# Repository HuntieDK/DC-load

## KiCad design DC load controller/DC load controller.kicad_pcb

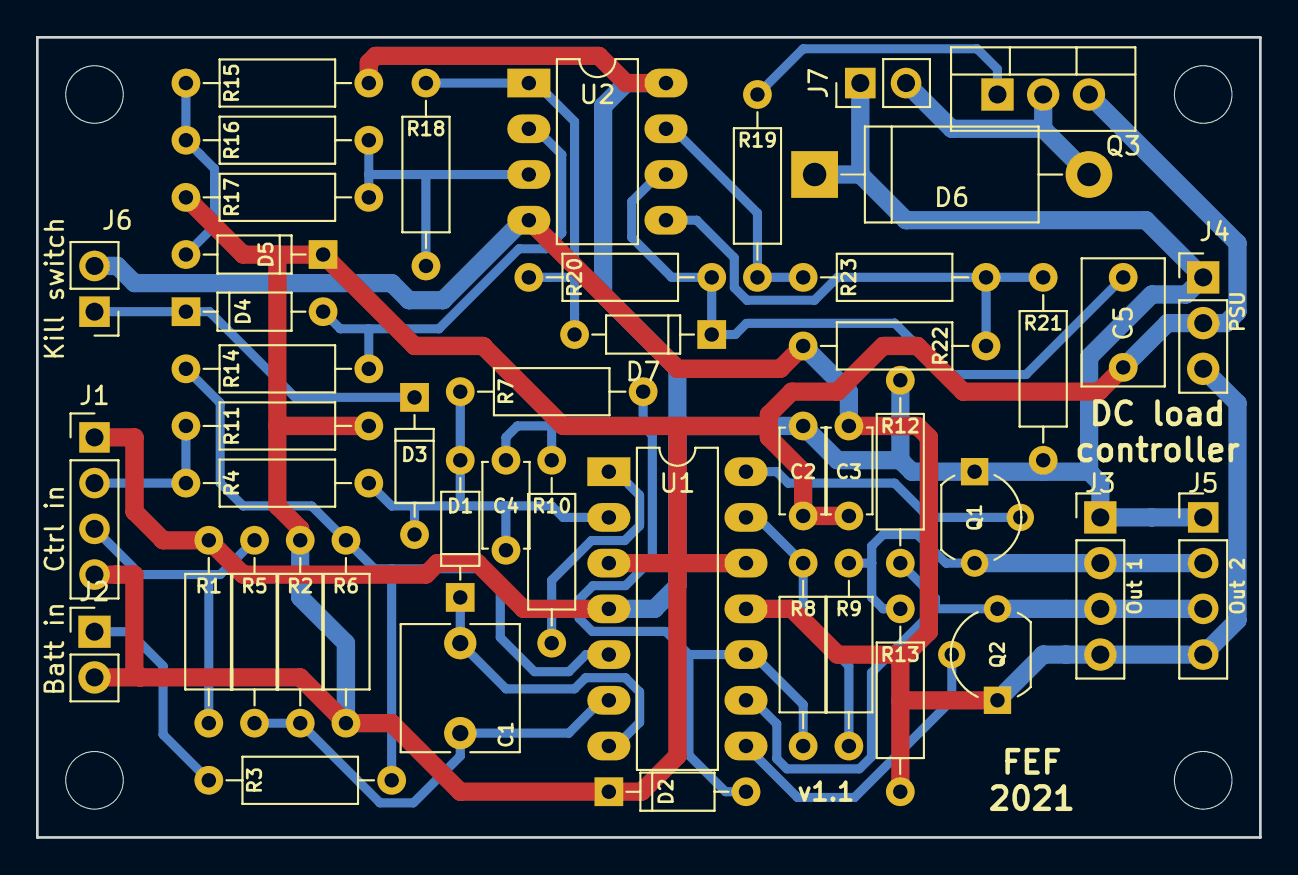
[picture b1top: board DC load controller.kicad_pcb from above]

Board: 2 copper layers, 67.9 x 44.5 mm, 51 parts (0 on the bottom side), 27 nets.

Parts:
C1: 2u2; C_Rect_L7.0mm_W6.5mm_P5.00mm
C2, C3: 100n; C_Disc_D4.7mm_W2.5mm_P5.00mm
C4: 10n; C_Disc_D4.7mm_W2.5mm_P5.00mm
C5: 220n; C_Rect_L7.0mm_W4.5mm_P5.00mm
D1, D3, D4, D5, D7: 1n4148; D_DO-35_SOD27_P7.62mm_Horizontal
D2: 5v6; D_DO-35_SOD27_P7.62mm_Horizontal
D6: 1n5403; D_DO-201_P15.24mm_Horizontal
J1: Ctrl In; PinHeader_1x04_P2.54mm_Vertical
J2: Batt in; Pin_Header_Straight_1x02_Pitch2.54mm
J3: Ctrl Out 1; Pin_Header_Straight_1x04_Pitch2.54mm
J4: Pwr in; Pin_Header_Straight_1x03_Pitch2.54mm
J5: Ctrl Out 2; Pin_Header_Straight_1x04_Pitch2.54mm
J6: Killswitch; Pin_Header_Straight_1x02_Pitch2.54mm
J7: Relay out; Pin_Header_Straight_1x02_Pitch2.54mm
M1, M2, M3, M4: 3mm; MountingHole_3.2mm_M3
Q1: BC337; TO-92_Molded_Wide
Q2: BC327; TO-92_Molded_Wide
Q3: IRF540N; TO-220-3_Vertical
R1: 66k5; R_Axial_DIN0207_L6.3mm_D2.5mm_P10.16mm_Horizontal
R2, R3, R4: 20k; R_Axial_DIN0207_L6.3mm_D2.5mm_P10.16mm_Horizontal
R5, R6: 2k; R_Axial_DIN0207_L6.3mm_D2.5mm_P10.16mm_Horizontal
R7, R8, R9, R15: 10k; R_Axial_DIN0207_L6.3mm_D2.5mm_P10.16mm_Horizontal
R10: 953; R_Axial_DIN0207_L6.3mm_D2.5mm_P10.16mm_Horizontal
R11, R12, R13, R23: 1k; R_Axial_DIN0207_L6.3mm_D2.5mm_P10.16mm_Horizontal
R14, R21, R22: 100k; R_Axial_DIN0207_L6.3mm_D2.5mm_P10.16mm_Horizontal
R16: 6k04; R_Axial_DIN0207_L6.3mm_D2.5mm_P10.16mm_Horizontal
R17, R19: 100; R_Axial_DIN0207_L6.3mm_D2.5mm_P10.16mm_Horizontal
R18: 1M2; R_Axial_DIN0207_L6.3mm_D2.5mm_P10.16mm_Horizontal
R20: 1M; R_Axial_DIN0207_L6.3mm_D2.5mm_P10.16mm_Horizontal
U1: LM324; DIP-14_W7.62mm_LongPads
U2: LM358; DIP-8_W7.62mm_LongPads

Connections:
GND: C2.2, C3.1, C5.2, D2.1, D5.1, J1.4, J2.2, J4.2, Q3.3, R5.2, R6.2, R11.2, R17.2, U1.3, U1.12
unnamed: C1.1, D1.1, U1.7
unnamed: C1.2, R2.2, R5.1, U1.6
unnamed: C4.1, D1.2, D3.2, R4.1, R7.2, U1.2
unnamed: C4.2, D2.2, R7.1, R8.2, R10.1, U1.10
unnamed: C5.1, D7.1, R20.2, U2.6
unnamed: D3.1, D4.1, J6.1
unnamed: D4.2, R14.1, U2.2
unnamed: D5.2, R15.1, R16.1
unnamed: D6.2, J7.2, Q3.2
unnamed: D7.2, R18.1, R20.1, U2.1
unnamed: J1.2, R4.2, R11.1
unnamed: J1.3, R1.2, R2.1
unnamed: J2.1, R3.2
unnamed: J3.2, J5.2, Q1.3, R9.2, R13.1
unnamed: J3.3, J5.3, Q2.3, R12.2, U1.9
unnamed: Q1.2, U1.14
unnamed: Q2.2, U1.8
unnamed: Q3.1, R19.1
unnamed: R8.1, R9.1, U1.13
unnamed: R10.2, U1.1
unnamed: R3.1, R6.1, R14.2, U1.5
unnamed: R16.2, R17.1, R18.2, U2.3
unnamed: R19.2, R23.1, U2.7
unnamed: R21.2, R22.1, R23.2, U2.5
VDD: C2.1, D6.1, J1.1, J3.1, J4.1, J5.1, J7.1, Q1.1, R1.1, R12.1, R15.2, R21.1, U1.4, U2.8
VSS: C3.2, J3.4, J4.3, J5.4, J6.2, Q2.1, R13.2, R22.2, U1.11, U2.4

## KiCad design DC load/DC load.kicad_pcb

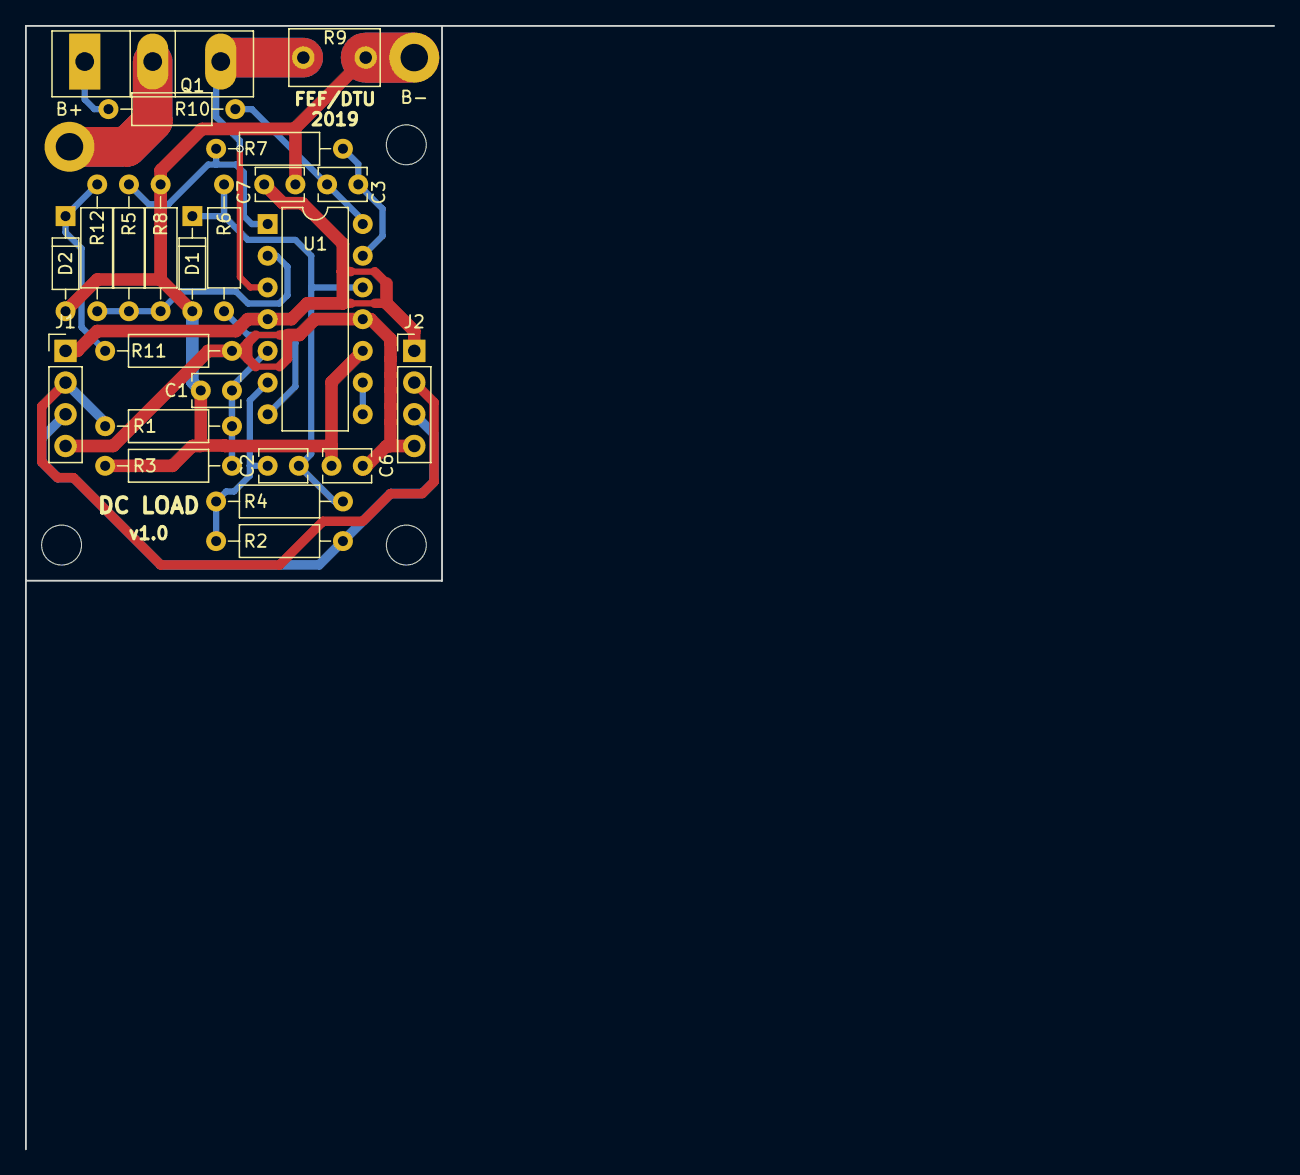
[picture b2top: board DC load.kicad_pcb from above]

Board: 2 copper layers, 100.0 x 90.0 mm, 28 parts (0 on the bottom side), 18 nets.

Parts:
C1, C2, C6, C7: 10n; C_Disc_D3.8mm_W2.6mm_P2.50mm
C3: 22n; C_Disc_D3.8mm_W2.6mm_P2.50mm
D1: 3v0/5mA; D_DO-35_SOD27_P7.62mm_Horizontal
D2: 1n4148; D_DO-35_SOD27_P7.62mm_Horizontal
J1: CTL IN; Pin_Header_Straight_1x04_Pitch2.54mm
J2: CTL OUT; Pin_Header_Straight_1x04_Pitch2.54mm
J3: B+; SolderWirePad_single_2-5mmDrill
J4: B-; SolderWirePad_single_2-5mmDrill
M2, M3, M3#2: 3.2mm; MountingHole_3.2mm_M3_DIN965
Q1: IRFP150NPBF; TO-247_TO-3P_Vertical
R1, R2, R7: 10k; R_Axial_DIN0207_L6.3mm_D2.5mm_P10.16mm_Horizontal
R3, R4: 2k49; R_Axial_DIN0207_L6.3mm_D2.5mm_P10.16mm_Horizontal
R5: 2k; R_Axial_DIN0207_L6.3mm_D2.5mm_P10.16mm_Horizontal
R6: 1k4; R_Axial_DIN0207_L6.3mm_D2.5mm_P10.16mm_Horizontal
R8, R10: 1k; R_Axial_DIN0207_L6.3mm_D2.5mm_P10.16mm_Horizontal
R9: 0R1 7W; C_Rect_L7.2mm_W4.5mm_P5.00mm_FKS2_FKP2_MKS2_MKP2
R11: 11k5; R_Axial_DIN0207_L6.3mm_D2.5mm_P10.16mm_Horizontal
R12: 127k; R_Axial_DIN0207_L6.3mm_D2.5mm_P10.16mm_Horizontal
U1: LM324; DIP-14_W7.62mm

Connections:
GND: C1.1, C6.2, C7.2, D1.2, D2.2, J4.1, R3.2, R8.2, R9.2, U1.10
unnamed: C1.2, R1.1, R3.1, U1.5
unnamed: C2.1, D1.1, R4.1, R6.2, U1.12
unnamed: C2.2, R2.1, R4.2, U1.6
unnamed: C3.1, R10.2, U1.14
unnamed: C3.2, R7.1, U1.13
unnamed: D2.1, R11.1, R12.2
unnamed: J1.2, J2.2, R1.2
unnamed: J1.3, J2.3, R2.2
unnamed: J3.1, Q1.2
unnamed: Q1.1, R10.1
unnamed: Q1.3, R9.1, U1.3
unnamed: R5.1, R7.2, U1.1
unnamed: R6.1, U1.7
unnamed: R5.2, R8.1, R12.1, U1.2
unnamed: U1.8, U1.9
VDD: C7.1, J1.1, J2.1, U1.4
VSS: C6.1, J1.4, J2.4, R11.2, U1.11

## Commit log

2019-02-04 Initial prototype version
2019-02-04 Figuring out 0V turn-off
2019-02-04 Diagram: * Small offset so 0V is guaranteed to shut current off * Added zener to avoid high voltages and polarity reversal PCB: * Layout updated to new schematics
2019-02-09 Version 0.3: Reverted to more conventional opamp usage
2019-02-10 Prepare for production
2019-02-11 Changed overcurrent limiter
2019-02-12 * Added controller with battery low voltage cut off and balancing * Reorganized folders
2019-02-12 PCB layout - wider power tracks
2019-02-16 Some stability and safety features added to controller
2019-03-03 New opamp selection for load controller (700mA output drive for controlling many loads)
2019-03-05 Some layout stuff
2019-03-05 Small layout fix
2019-03-17 L272A prototype 2 (first was unstable)
2019-03-17 Added output driver transistors
2019-03-19 Added extra output socket Layout changes
2019-03-20 Fix wrong wire in schematics and pcb
2019-03-30 Some layout changes (smaller capacitor outlines; more space for connectors)
2019-03-31 New TO247 housed FET for better dissipation
2019-03-31 Layout fixes
2020-02-03 Controller enhancements
    Safety relay control
    Input polarity check
2021-12-15 Updated kicad version
